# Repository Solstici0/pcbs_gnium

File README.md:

# pcbs_gnium
kicad projects containing the different gnium line follower robot

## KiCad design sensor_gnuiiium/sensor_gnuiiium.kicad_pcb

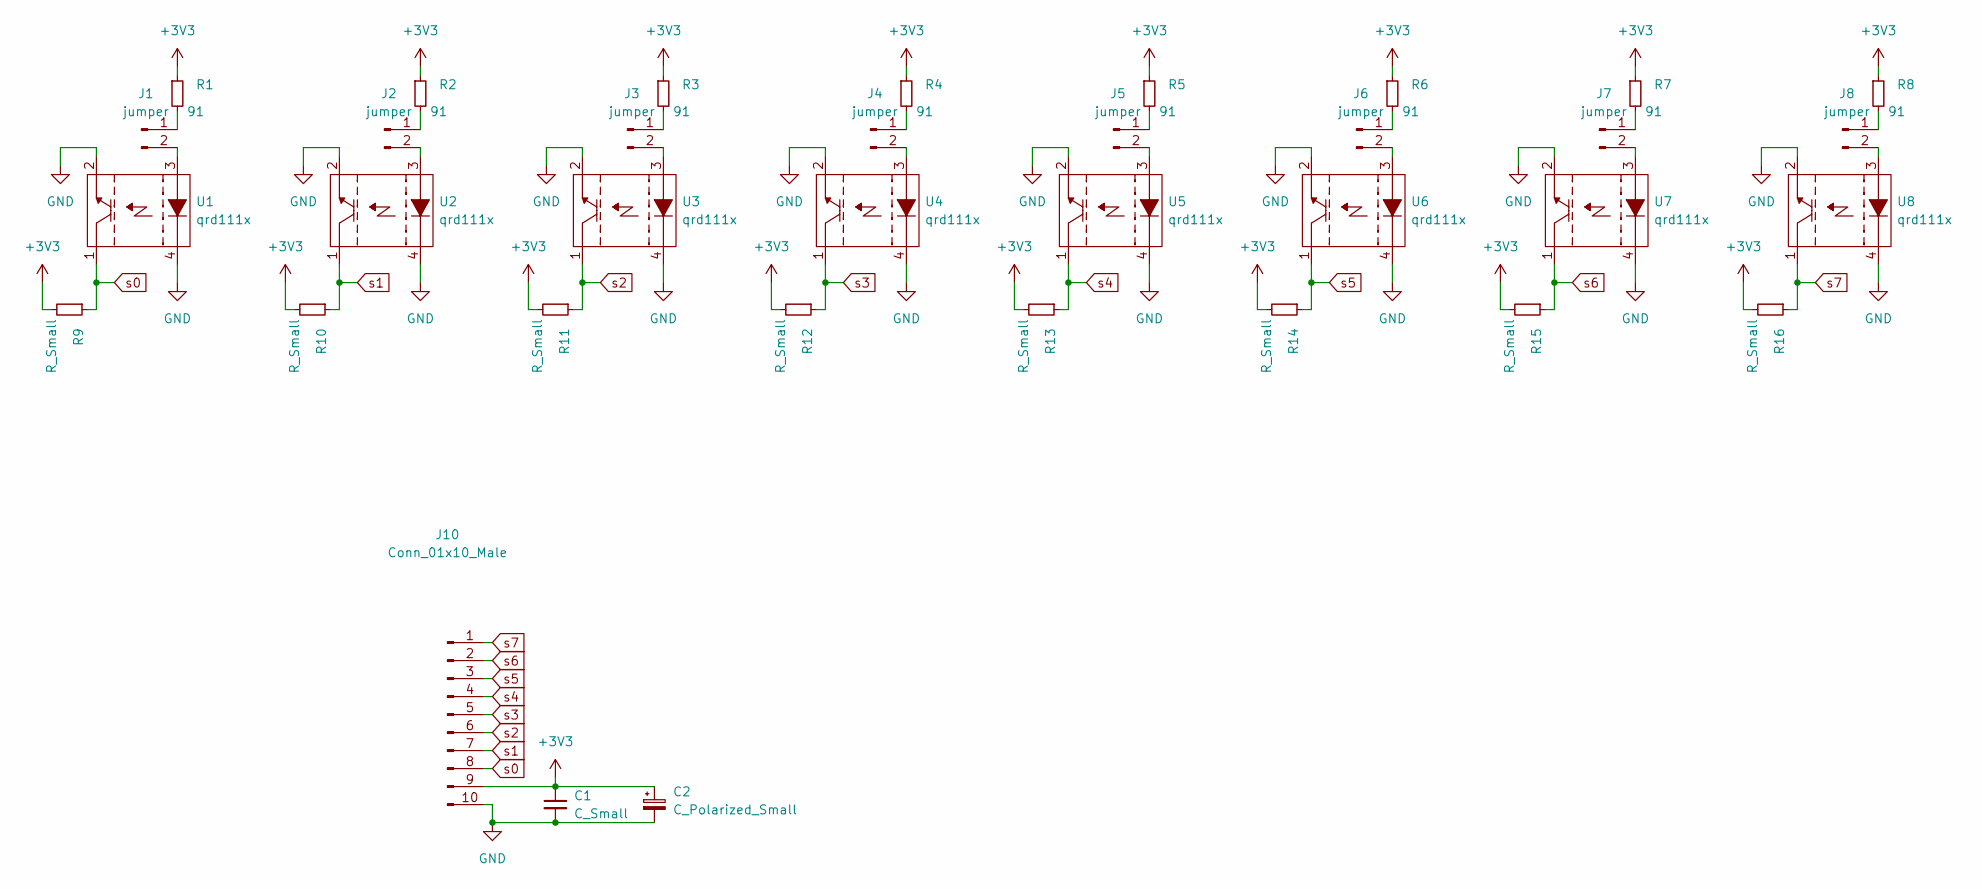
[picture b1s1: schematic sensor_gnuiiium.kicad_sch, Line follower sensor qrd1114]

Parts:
C1: C_Small; C_Axial_L3.8mm_D2.6mm_P7.50mm_Horizontal
C2: C_Polarized_Small; CP_Radial_D8.0mm_P5.00mm
J1, J2, J3, J4, J5, J6, J7, J8: jumper; PinSocket_1x02_P2.54mm_Vertical
J10: Conn_01x10_Male; PinSocket_1x10_P2.54mm_Vertical
R1, R2, R3, R4, R5, R6, R7, R8: 91; R_0805_2012Metric_Pad1.20x1.40mm_HandSolder
R9, R10, R11, R12, R13, R14, R15, R16: R_Small; R_0805_2012Metric_Pad1.20x1.40mm_HandSolder
U1, U2, U3, U4, U5, U6, U7, U8: qrd111x

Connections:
+3V3: C1.1, C2.1, J10.9, R1.1, R2.1, R3.1, R4.1, R5.1, R6.1, R7.1, R8.1, R9.2, R10.2, R11.2, R12.2, R13.2, R14.2, R15.2, R16.2
GND: C1.2, C2.2, J10.10, U1.2, U1.4, U2.2, U2.4, U3.2, U3.4, U4.2, U4.4, U5.2, U5.4, U6.2, U6.4, U7.2, U7.4, U8.2, U8.4
unnamed: J1.1, R1.2
unnamed: J1.2, U1.3
unnamed: J2.1, R2.2
unnamed: J2.2, U2.3
unnamed: J3.1, R3.2
unnamed: J3.2, U3.3
unnamed: J4.1, R4.2
unnamed: J4.2, U4.3
unnamed: J5.1, R5.2
unnamed: J5.2, U5.3
unnamed: J6.1, R6.2
unnamed: J6.2, U6.3
unnamed: J7.1, R7.2
unnamed: J7.2, U7.3
unnamed: J8.1, R8.2
unnamed: J8.2, U8.3
s0: J10.8, R9.1, U1.1
s1: J10.7, R10.1, U2.1
s2: J10.6, R11.1, U3.1
s3: J10.5, R12.1, U4.1
s4: J10.4, R13.1, U5.1
s5: J10.3, R14.1, U6.1
s6: J10.2, R15.1, U7.1
s7: J10.1, R16.1, U8.1

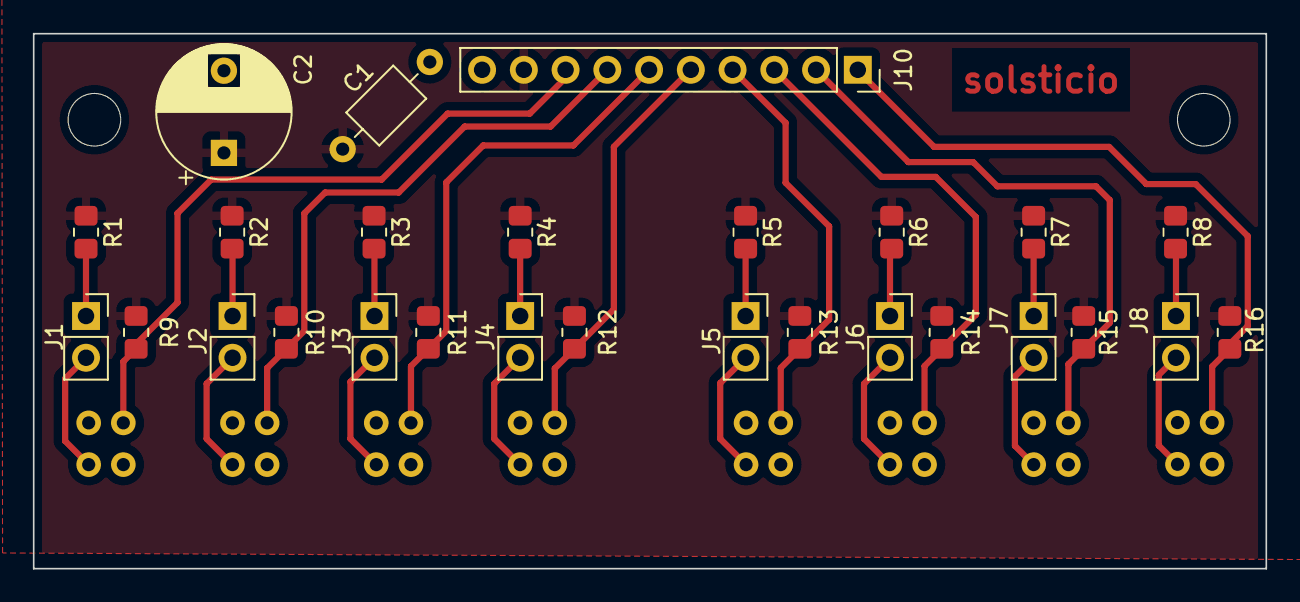
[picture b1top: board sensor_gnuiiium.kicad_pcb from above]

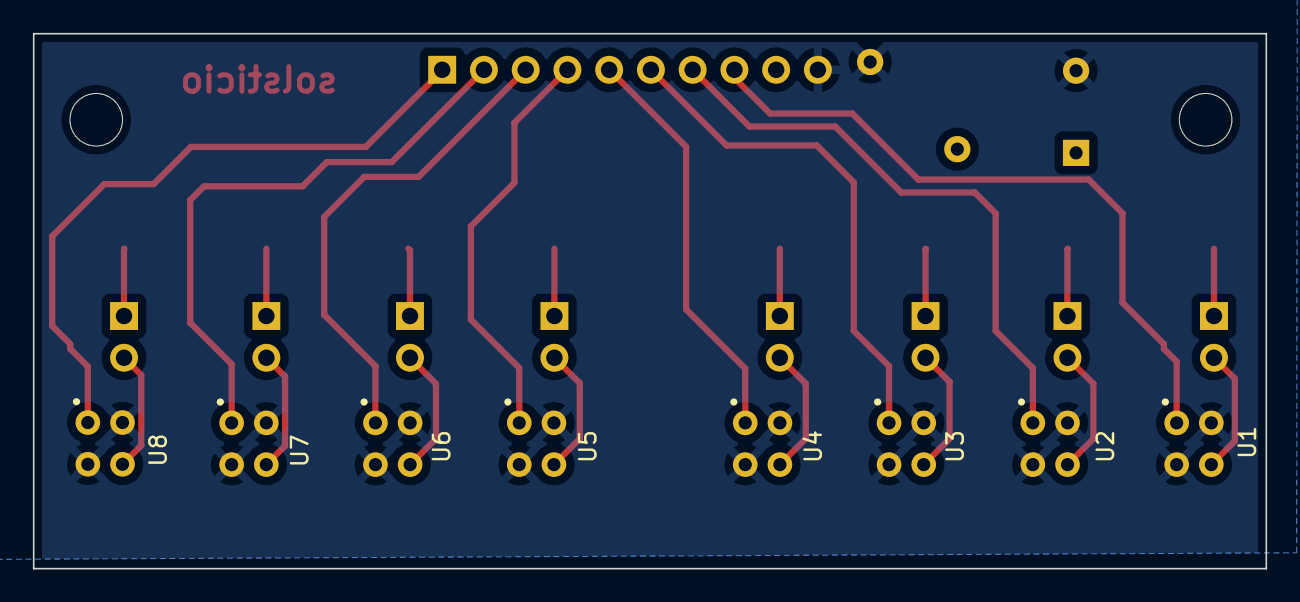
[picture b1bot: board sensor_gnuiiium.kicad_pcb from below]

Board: 2 copper layers, 75.0 x 32.5 mm, 35 parts (8 on the bottom side), 26 nets.

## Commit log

2022-07-29 added sensor pcb, TBT
2022-07-29 generated gerber files
2022-07-30 Flipped the sensors
2022-09-07 changed to smd version
2022-09-28 generated .step
2022-11-17 added side sensors
2022-11-17 added side_sensors
